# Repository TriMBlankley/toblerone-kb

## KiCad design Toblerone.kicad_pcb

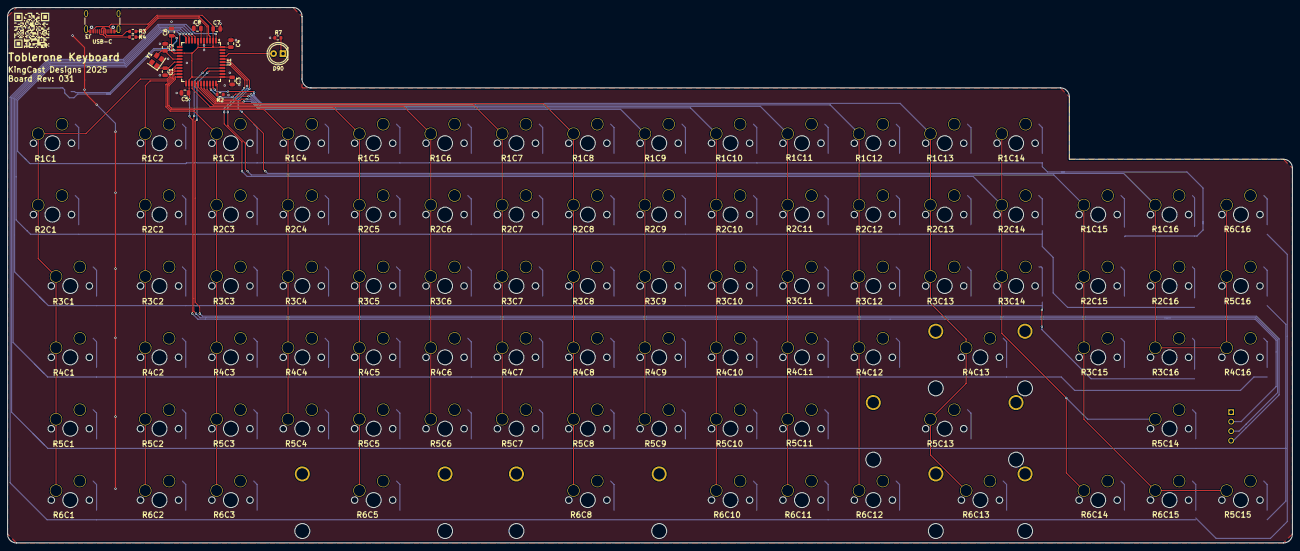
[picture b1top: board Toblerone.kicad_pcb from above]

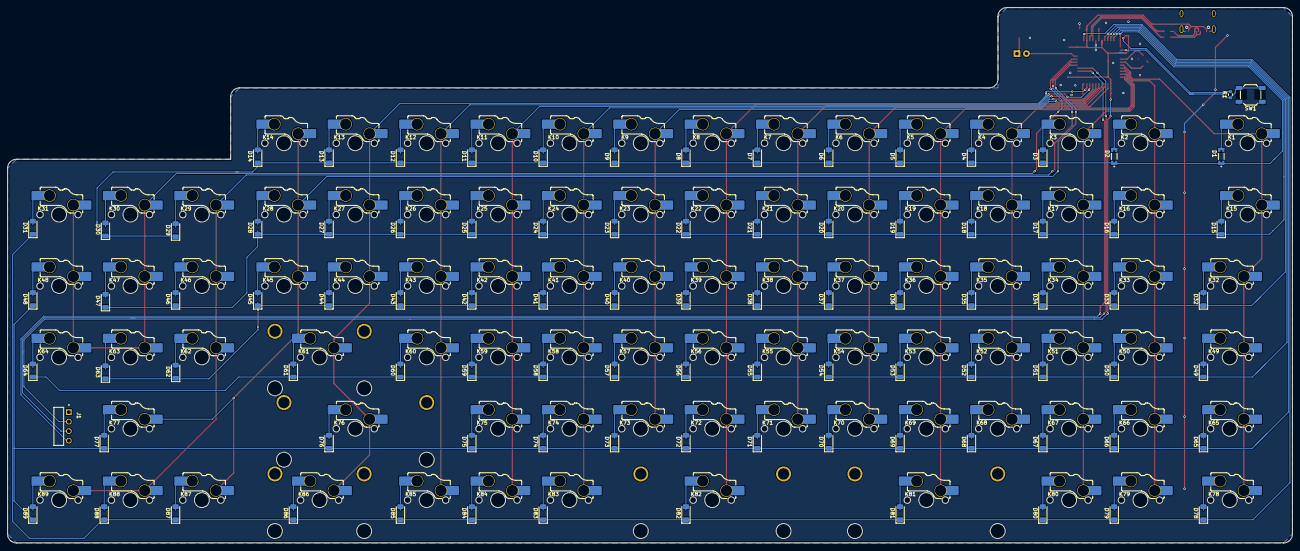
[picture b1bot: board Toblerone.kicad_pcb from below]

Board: 2 copper layers, 342.9 x 142.9 mm, 202 parts (181 on the bottom side), 126 nets.

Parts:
C1, C2: 22p; C_0805_2012Metric
C3, C4, C5, C6: 0.1u; C_0805_2012Metric
C7: 4.7u; C_0805_2012Metric
C8: 1u; C_0805_2012Metric
D1, D2: D; DIO_LL4148
D3, D4, D5, D6, D7, D8, D9, D10, D11, D12, D13, D14, D15, D16, D17, D18, D19, D20, D21, D22, D23, D24, D25, D26, D27, D28, D29, D30, D31, D32, D33, D34, D35, D36, D37, D38, D39, D40, D41, D42, D43, D44, D45, D46, D47, D48, D49, D50, D51, D52, D53, D54, D55, D56, D57, D58, D59, D60, D61, D62, D63, D64, D65, D66, D67, D68, D69, D70, D71, D72, D73, D74, D75, D76, D77, D78, D79, D80, D81, D82, D83, D84, D85, D86, D87, D88, D89: D; D_MiniMELF
D90: LED; LED_D5.0mm
J1: Conn_01x04_Pin; AMPHENOL_861400041LO1705LF
J3: USB_C_Receptacle_USB2.0_14P; USB_C_Receptacle_GCT_USB4105-xx-A_16P_TopMnt_Horizontal
K1, K2, K3, K4, K5, K6, K7, K8, K9, K10, K11, K12, K13, K14, K15, K16, K17, K18, K19, K20, K21, K22, K23, K24, K25, K26, K27, K28, K29, K30, K31, K32, K33, K34, K35, K36, K37, K38, K39, K40, K41, K42, K43, K44, K45, K46, K47, K48, K49, K50, K51, K52, K53, K54, K55, K56, K57, K58, K59, K60, K61, K62, K63, K64, K65, K66, K67, K68, K69, K70, K71, K72, K73, K74, K75, K76, K77, K78, K79, K80, K81, K82, K83, K84, K85, K86, K87, K88, K89: KEYSW; SW_MX_HS_KS-2P02B01-01_1u
R1, R2, R7: 10k; R_0603_1608Metric
R3, R4: 22; R_0603_1608Metric
S1, S2, S3: MX_stab_3u; STAB_MX_P_3u
S4, S5: MX_stab_2u; STAB_MX_P_2u
SW1: SW_PUSH; SW_SPST_SKQG_WithStem
U1: ATmega32U4-A; TQFP-44_10x10mm_P0.8mm
Y1: Crystal_GND24; Crystal_SMD_SeikoEpson_FA238-4Pin_3.2x2.5mm

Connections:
/Col1: K1.1, K15.1, K32.1, K49.1, K65.1, K78.1, U1.18 (PD0)
/Col2: K2.1, K16.1, K33.1, K50.1, K66.1, K79.1, U1.19 (PD1)
/Col3: K3.1, K17.1, K34.1, K51.1, K67.1, K80.1, U1.20 (PD2)
/Col4: K4.1, K18.1, K35.1, K52.1, K68.1, U1.21 (PD3)
/Col5: K5.1, K19.1, K36.1, K53.1, K69.1, K81.1, U1.22 (PD5)
/Col6: K6.1, K20.1, K37.1, K54.1, K70.1, U1.25 (PD4)
/Col7: K7.1, K21.1, K38.1, K55.1, K71.1, U1.26 (PD6)
/Col8: K8.1, K22.1, K39.1, K56.1, K72.1, K82.1, U1.27 (PD7)
/Col9: K9.1, K23.1, K40.1, K57.1, K73.1, U1.28 (PB4)
/Col10: K10.1, K24.1, K41.1, K58.1, K74.1, K83.1, U1.29 (PB5)
/Col11: K11.1, K25.1, K42.1, K59.1, K75.1, K84.1, U1.30 (PB6)
/Col12: K12.1, K26.1, K43.1, K60.1, K85.1, U1.31 (PC6)
/Col13: K13.1, K27.1, K44.1, K61.1, K76.1, K86.1, U1.32 (PC7)
/Col14: K14.1, K28.1, K45.1, K77.1, K87.1, U1.38 (PF5)
/Col15: K29.1, K46.1, K62.1, K88.1, K89.1, U1.39 (PF4)
/Col16: K30.1, K31.1, K47.1, K48.1, K63.1, K64.1, U1.40 (PF1)
/Row1: D1.C, D2.C, D3.1 (K), D4.1 (K), D5.1 (K), D6.1 (K), D7.1 (K), D8.1 (K), D9.1 (K), D10.1 (K), D11.1 (K), D12.1 (K), D13.1 (K), D14.1 (K), D29.1 (K), D30.1 (K), U1.12 (PB7)
/Row2: D15.1 (K), D16.1 (K), D17.1 (K), D18.1 (K), D19.1 (K), D20.1 (K), D21.1 (K), D22.1 (K), D23.1 (K), D24.1 (K), D25.1 (K), D26.1 (K), D27.1 (K), D28.1 (K), D46.1 (K), D47.1 (K), U1.11 (PB3)
/Row3: D32.1 (K), D33.1 (K), D34.1 (K), D35.1 (K), D36.1 (K), D37.1 (K), D38.1 (K), D39.1 (K), D40.1 (K), D41.1 (K), D42.1 (K), D43.1 (K), D44.1 (K), D45.1 (K), D62.1 (K), D63.1 (K), U1.10 (PB2)
/Row4: D49.1 (K), D50.1 (K), D51.1 (K), D52.1 (K), D53.1 (K), D54.1 (K), D55.1 (K), D56.1 (K), D57.1 (K), D58.1 (K), D59.1 (K), D60.1 (K), D61.1 (K), D64.1 (K), U1.9 (PB1)
/Row5: D48.1 (K), D65.1 (K), D66.1 (K), D67.1 (K), D68.1 (K), D69.1 (K), D70.1 (K), D71.1 (K), D72.1 (K), D73.1 (K), D74.1 (K), D75.1 (K), D76.1 (K), D77.1 (K), D89.1 (K), U1.8 (PB0)
/Row6: D31.1 (K), D78.1 (K), D79.1 (K), D80.1 (K), D81.1 (K), D82.1 (K), D83.1 (K), D84.1 (K), D85.1 (K), D86.1 (K), D87.1 (K), D88.1 (K), U1.1 (PE6)
/capslock: D90.2, U1.41 (PF0)
GND: C1.1, C2.1, C3.2, C4.2, C5.2, C6.2, C7.2, C8.2, J3.A1 (GND), J3.A12 (GND), J3.B1 (GND), J3.B12 (GND), J3.S1 (SHIELD), R2.2, R7.2, SW1.1, U1.5 (UGND), U1.15 (GND), U1.23 (GND), U1.35 (GND), U1.43 (GND), Y1.2, Y1.4
unnamed: D1.A, K1.2
unnamed: D2.A, K2.2
unnamed: D3.2 (A), K3.2
unnamed: D4.2 (A), K4.2
unnamed: D5.2 (A), K5.2
unnamed: D6.2 (A), K6.2
unnamed: D7.2 (A), K7.2
unnamed: D8.2 (A), K8.2
unnamed: D9.2 (A), K9.2
unnamed: D10.2 (A), K10.2
unnamed: D11.2 (A), K11.2
unnamed: D12.2 (A), K12.2
unnamed: D13.2 (A), K13.2
unnamed: D14.2 (A), K14.2
unnamed: D15.2 (A), K15.2
unnamed: D16.2 (A), K16.2
unnamed: D17.2 (A), K17.2
unnamed: D18.2 (A), K18.2
unnamed: D19.2 (A), K19.2
unnamed: D20.2 (A), K20.2
unnamed: D21.2 (A), K21.2
unnamed: D22.2 (A), K22.2
unnamed: D23.2 (A), K23.2
unnamed: D24.2 (A), K24.2
unnamed: D25.2 (A), K25.2
unnamed: D26.2 (A), K26.2
unnamed: D27.2 (A), K27.2
unnamed: D28.2 (A), K28.2
unnamed: D29.2 (A), K29.2
unnamed: D30.2 (A), K30.2
unnamed: D31.2 (A), K31.2
unnamed: D32.2 (A), K32.2
unnamed: D33.2 (A), K33.2
unnamed: D34.2 (A), K34.2
unnamed: D35.2 (A), K35.2
unnamed: D36.2 (A), K36.2
unnamed: D37.2 (A), K37.2
unnamed: D38.2 (A), K38.2
unnamed: D39.2 (A), K39.2
unnamed: D40.2 (A), K40.2
unnamed: D41.2 (A), K41.2
unnamed: D42.2 (A), K42.2
unnamed: D43.2 (A), K43.2
unnamed: D44.2 (A), K44.2
unnamed: D45.2 (A), K45.2
unnamed: D46.2 (A), K46.2
unnamed: D47.2 (A), K47.2
unnamed: D48.2 (A), K48.2
unnamed: D49.2 (A), K49.2
unnamed: D50.2 (A), K50.2
unnamed: D51.2 (A), K51.2
unnamed: D52.2 (A), K52.2
unnamed: D53.2 (A), K53.2
unnamed: D54.2 (A), K54.2
unnamed: D55.2 (A), K55.2
unnamed: D56.2 (A), K56.2
unnamed: D57.2 (A), K57.2
unnamed: D58.2 (A), K58.2
unnamed: D59.2 (A), K59.2
unnamed: D60.2 (A), K60.2
unnamed: D61.2 (A), K61.2
unnamed: D62.2 (A), K62.2
unnamed: D63.2 (A), K63.2
unnamed: D64.2 (A), K64.2
unnamed: D65.2 (A), K65.2
unnamed: D66.2 (A), K66.2
unnamed: D67.2 (A), K67.2
unnamed: D68.2 (A), K68.2
unnamed: D69.2 (A), K69.2
unnamed: D70.2 (A), K70.2
unnamed: D71.2 (A), K71.2
unnamed: D72.2 (A), K72.2
unnamed: D73.2 (A), K73.2
unnamed: D74.2 (A), K74.2
unnamed: D75.2 (A), K75.2
unnamed: D76.2 (A), K76.2
unnamed: D77.2 (A), K77.2
unnamed: D78.2 (A), K78.2
unnamed: D79.2 (A), K79.2
unnamed: D80.2 (A), K80.2
unnamed: D81.2 (A), K81.2
unnamed: D82.2 (A), K82.2
unnamed: D83.2 (A), K83.2
unnamed: D84.2 (A), K84.2
unnamed: D85.2 (A), K85.2
unnamed: D86.2 (A), K86.2
unnamed: D87.2 (A), K87.2
unnamed: D88.2 (A), K88.2
unnamed: D89.2 (A), K89.2
unnamed: D90.1, R7.1
unnamed: J1.03, U1.37 (PF6)
unnamed: J1.04, U1.36 (PF7)
unnamed: J3.A6 (D+), J3.B6 (D+), R4.2
unnamed: J3.A7 (D-), J3.B7 (D-), R3.2
unnamed: R4.1, U1.4 (D+)
unnamed: R3.1, U1.3 (D-)
unnamed: C8.1, U1.6 (UCAP)
unnamed: C1.2, U1.17 (XTAL1), Y1.1
unnamed: C2.2, U1.16 (XTAL2), Y1.3
unnamed: R2.1, U1.33 (~HWB/PE2)
unnamed: R1.2, SW1.2, U1.13 (~RESET)
VCC: C3.1, C4.1, C5.1, C6.1, C7.1, J1.02, J3.A4 (VBUS), J3.A9 (VBUS), J3.B4 (VBUS), J3.B9 (VBUS), R1.1, U1.2 (UVCC), U1.7 (VBUS), U1.14 (VCC), U1.24 (AVCC), U1.34 (VCC), U1.44 (AVCC)

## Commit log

2025-10-05 Kinda cursed but here's a submodule
2025-10-06 PCB design is complete
2026-02-01 Pushing solidworks files
